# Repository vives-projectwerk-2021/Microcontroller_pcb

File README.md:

# Microcontroller_pcb

Kicad files for our microcontroller pcb

## Schematic

You can see the updated schematic of our main board in the picture below

## Pictures

| Front | Back |
|---|---|
|In this picture you can see the front of the pcb|In this picture you can see the back of the pcb
| |  |

## Components

- STM32L476RGT

- 32768 Crystal

- ESD Protection(USBLC6-2SC6)

- L432KC pin layout

- Cryptochip (ATTEC508A)

- Batteryholder(1013)

- LoraModule (RFM95W)

- Lichtsensor (LTR-329ALS)

- 2x Button switch SMD

- 18x 100nF (0603) condensatoren

- 2x 4pf (0603) Condensator bij crystal

- LED SMD (0805)

- 2x Fuse (0603)

- Temperaturesensor TCN75AVUA713-VAO

- EEPROM geheugen 24AA64T

- Connector Antenne SMA_Amphenol

- Connector voor moisture 2x03 2.54mm

- USB-C Connector 2.0 Type-c-31-m-12

- Connector voor batterij 1x03 2.54mm

- 2x Connector Molex 1x08 2.00mm

- SWD Programming port (20021521-00010T1LF)

- 2x LDO (PS1 S-1318B33-M5T1U4)

- 1x 4.7kΩ

- 2x 5.1kΩ

- 3x 360Ω

- 2x 100kΩ

- 1x 220kΩ

- 1x 330kΩ

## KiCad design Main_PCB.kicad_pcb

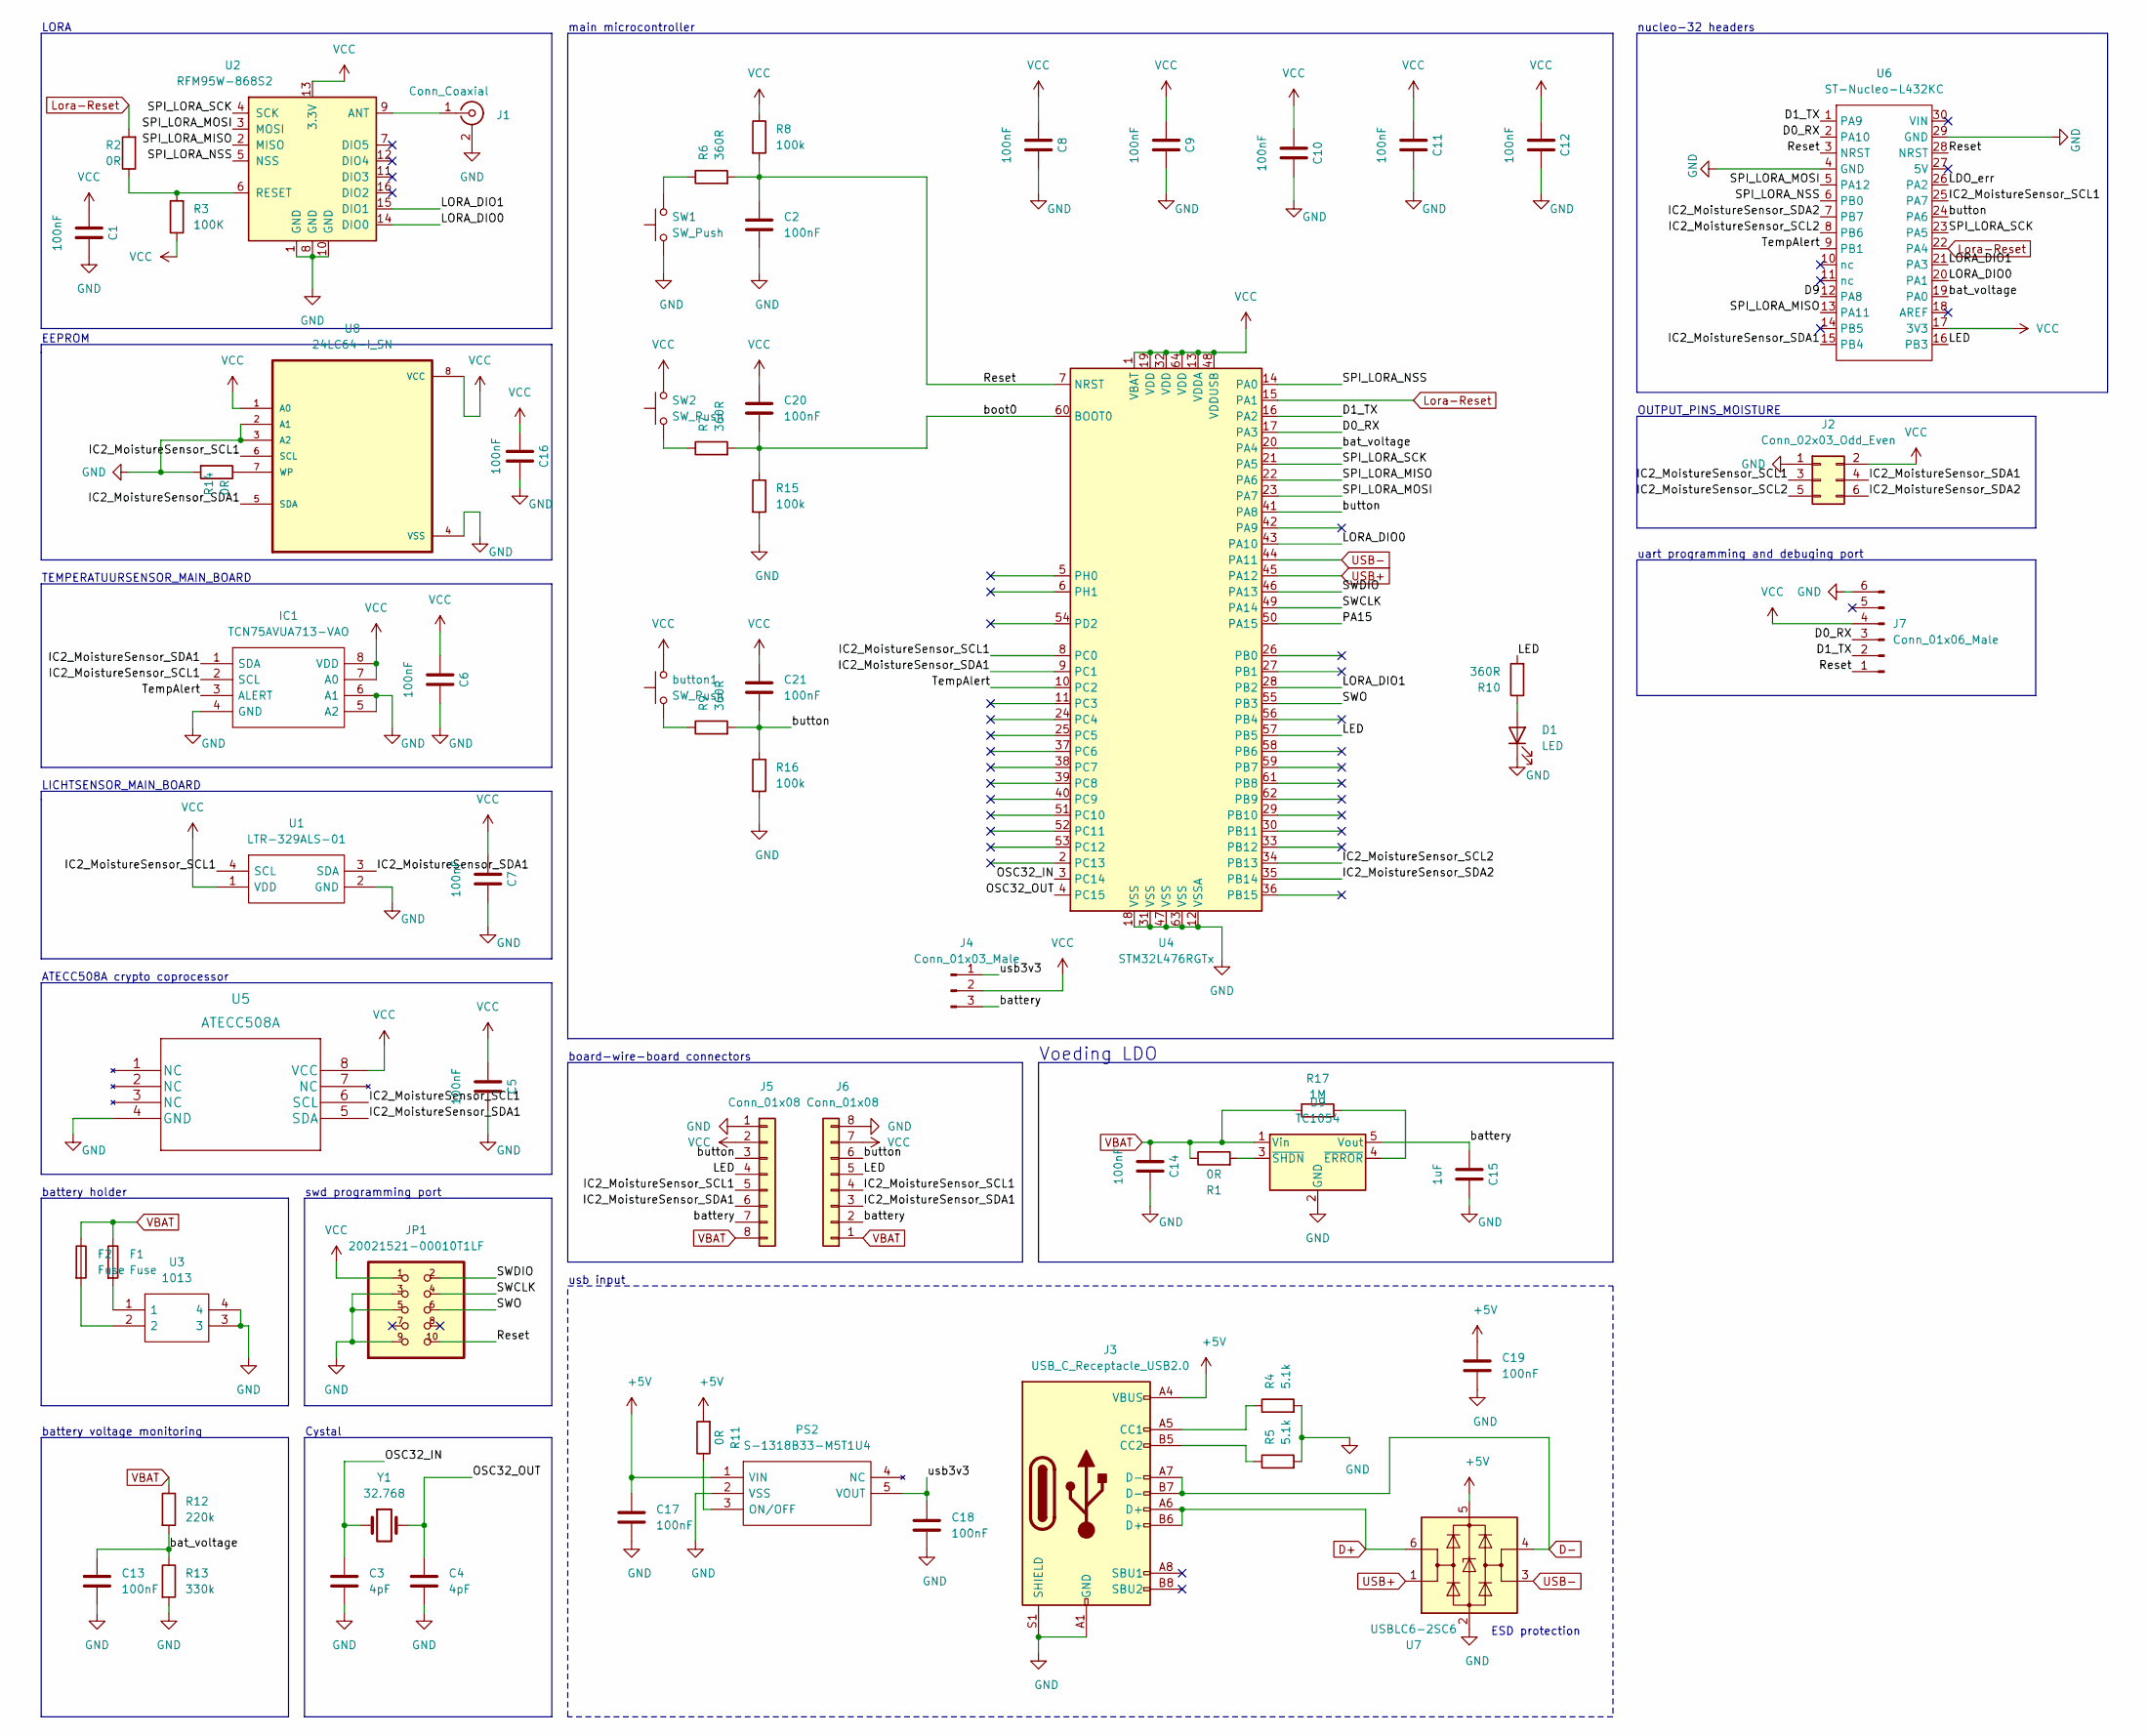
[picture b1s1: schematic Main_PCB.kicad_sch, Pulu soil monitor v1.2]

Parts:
C1, C2, C5, C6, C7, C8, C9, C10, C11, C12, C13, C14, C16, C17, C18, C19, C20, C21: 100nF; C_0603_1608Metric_Pad1.08x0.95mm_HandSolder
C3, C4: 4pF; C_0603_1608Metric_Pad1.08x0.95mm_HandSolder
C15: 1uF; C_0805_2012Metric_Pad1.18x1.45mm_HandSolder
D1: LED; LED_0805_2012Metric_Pad1.15x1.40mm_HandSolder
F1, F2: Fuse; Fuse_0603_1608Metric_Pad1.05x0.95mm_HandSolder
IC1: TCN75AVUA713-VAO; SOP65P490X110-8N; Manufacturer_Part_Number TCN75AVUA713-VAO; Mouser Part Number 579-TCN75AVUA713-VAO
J1: Conn_Coaxial; SMA_Amphenol_901-144_Vertical
J2: Conn_02x03_Odd_Even; IDC-Header_2x03_P2.54mm_Vertical
J3: USB_C_Receptacle_USB2.0; USB_C_Receptacle_HRO_TYPE-C-31-M-12
J4: Conn_01x03_Male; PinHeader_1x03_P2.54mm_Vertical
J5, J6: Conn_01x08; Molex_Micro-Latch_53253-0870_1x08_P2.00mm_Vertical
J7: Conn_01x06_Male; PinHeader_1x06_P2.54mm_Vertical
JP1: 20021521-00010T1LF
PS2: S-1318B33-M5T1U4; SOT95P275X130-5N; Manufacturer_Part_Number S-1318B33-M5T1U4; Mouser Part Number 628-S-1318B33-M5T1U4
R1, R2, R11, R14: 0R; R_0603_1608Metric_Pad0.98x0.95mm_HandSolder
R3: 100K; R_0603_1608Metric_Pad0.98x0.95mm_HandSolder
R4, R5: 5.1k; R_0603_1608Metric_Pad0.98x0.95mm_HandSolder
R6, R7, R9, R10: 360R; R_0603_1608Metric_Pad0.98x0.95mm_HandSolder
R8, R15, R16: 100k; R_0603_1608Metric_Pad0.98x0.95mm_HandSolder
R12: 220k; R_0603_1608Metric_Pad0.98x0.95mm_HandSolder
R13: 330k; R_0603_1608Metric_Pad0.98x0.95mm_HandSolder
R17: 1M; R_0612_1632Metric_Pad1.18x3.40mm_HandSolder
SW1, SW2: SW_Push; SW_SPST_TL3342
U1: LTR-329ALS-01; LTR329ALS01; Manufacturer_Part_Number LTR-329ALS-01; Mouser Part Number 859-LTR-329ALS-01
U2: RFM95W-868S2; XCVR_RFM95W-868S2
U3: 1013; Manufacturer_Part_Number 1013; Mouser Part Number 534-1013
U4: STM32L476RGTx; LQFP-64_10x10mm_P0.5mm
U5: ATECC508A; ATECC508A-SSHDA-T
U6: ST-Nucleo-L432KC
U7: USBLC6-2SC6; SOT-23-6
U8: 24LC64-I_SN; SOP-8_3.9x4.9mm_P1.27mm
U9: TC1054; SOT-23-5
Y1: 32.768; Crystal_SMD_3215-2Pin_3.2x1.5mm
button1: SW_Push; SW_SPST_TL3342

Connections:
+5V: C17.1, C19.1, J3.A4 (VBUS), J3.A9 (VBUS), J3.B4 (VBUS), J3.B9 (VBUS), PS2.1 (VIN), R11.2, U7.5 (VBUS)
/D0_RX: J7.3, U4.17 (PA3), U6.2 (PA10)
/D1_TX: J7.2, U4.16 (PA2), U6.1 (PA9)
/D9: U6.12 (PA8)
/IC2_MoistureSensor_SCL1: IC1.2 (SCL), J2.3, J5.5, J6.4, U1.4 (SCL), U4.8 (PC0), U5.6 (SCL), U6.25 (PA7), U8.6 (SCL)
/IC2_MoistureSensor_SCL2: J2.5, U4.34 (PB13), U6.8 (PB6)
/IC2_MoistureSensor_SDA1: IC1.1 (SDA), J2.4, J5.6, J6.3, U1.3 (SDA), U4.9 (PC1), U5.5 (SDA), U6.15 (PB4), U8.5 (SDA)
/IC2_MoistureSensor_SDA2: J2.6, U4.35 (PB14), U6.7 (PB7)
/LDO_err: U6.26 (PA2)
/LED: J5.4, J6.5, R10.2, U4.57 (PB5), U6.16 (PB3)
/LORA_DIO0: U2.14 (DIO0), U4.43 (PA10), U6.20 (PA1)
/LORA_DIO1: U2.15 (DIO1), U4.28 (PB2), U6.21 (PA3)
/OSC32_IN: C3.1, U4.3 (PC14), Y1.1
/OSC32_OUT: C4.1, U4.4 (PC15), Y1.2
/PA15: U4.50 (PA15)
/Reset: C2.1, J7.1, JP1.10, R6.2, R8.2, U4.7 (NRST), U6.3 (NRST), U6.28 (NRST)
/SPI_LORA_MISO: U2.2 (MISO), U4.22 (PA6), U6.13 (PA11)
/SPI_LORA_MOSI: U2.3 (MOSI), U4.23 (PA7), U6.5 (PA12)
/SPI_LORA_NSS: U2.5 (NSS), U4.14 (PA0), U6.6 (PB0)
/SPI_LORA_SCK: U2.4 (SCK), U4.21 (PA5), U6.23 (PA5)
/SWCLK: JP1.4, U4.49 (PA14)
/SWDIO: JP1.2, U4.46 (PA13)
/SWO: JP1.6, U4.55 (PB3)
/TempAlert: IC1.3 (ALERT), U4.10 (PC2), U6.9 (PB1)
/bat_voltage: C13.1, R12.2, R13.1, U4.20 (PA4), U6.19 (PA0)
/battery: C15.2, J4.3, J5.7, J6.2, U9.5 (Vout)
/boot0: C20.2, R7.2, R15.1, U4.60 (BOOT0)
/button: C21.2, J5.3, J6.6, R9.2, R16.1, U4.41 (PA8), U6.24 (PA6)
/usb3v3: C18.1, J4.1, PS2.5 (VOUT)
D+: J3.A6 (D+), J3.B6 (D+), U7.6 (I/O1)
D-: J3.A7 (D-), J3.B7 (D-), U7.4 (I/O2)
GND: C1.1, C2.2, C3.2, C4.2, C5.1, C6.1, C7.1, C8.1, C9.1, C10.1, C11.1, C12.1, C13.2, C14.1, C15.1, C16.1, C17.2, C18.2, C19.2, D1.1 (K), IC1.4 (GND), IC1.5 (A2), IC1.6 (A1), J1.2 (Ext), J2.1, J3.A1 (GND), J3.A12 (GND), J3.B1 (GND), J3.B12 (GND), J3.S1 (SHIELD), J5.1, J6.8, J7.6, JP1.3, JP1.5, JP1.9, PS2.2 (VSS), R4.2, R5.2, R13.2, R14.2, R15.2, R16.2, SW1.1, U1.2 (GND), U2.1 (GND), U2.8 (GND), U2.10 (GND), U3.3, U3.4, U4.12 (VSSA), U4.18 (VSS), U4.31 (VSS), U4.47 (VSS), U4.63 (VSS), U5.4 (GND), U6.4 (GND), U6.29 (GND), U7.2 (GND), U8.2 (A1), U8.3 (A2), U8.4 (VSS), U9.2 (GND)
Lora-Reset: R2.2, U4.15 (PA1), U6.22 (PA4)
unnamed: D1.2 (A), R10.1
unnamed: F1.2, U3.1
unnamed: F2.2, U3.2
unnamed: J1.1 (In), U2.9 (ANT)
unnamed: J3.A5 (CC1), R4.1
unnamed: J3.B5 (CC2), R5.1
unnamed: PS2.3 (ON/OFF), R11.1
unnamed: R1.2, U9.3 (~SHDN)
unnamed: R2.1, R3.2, U2.6 (RESET)
unnamed: R6.1, SW1.2
unnamed: R7.1, SW2.1
unnamed: R9.1, button1.1
unnamed: R14.1, U8.7 (WP)
unnamed: R17.1, U9.4 (~ERROR)
USB+: U4.45 (PA12), U7.1 (I/O1)
USB-: U4.44 (PA11), U7.3 (I/O2)
VBAT: C14.2, F1.1, F2.1, J5.8, J6.1, R1.1, R12.1, R17.2, U9.1 (Vin)
VCC: C1.2, C5.2, C6.2, C7.2, C8.2, C9.2, C10.2, C11.2, C12.2, C16.2, C20.1, C21.1, IC1.7 (A0), IC1.8 (VDD), J2.2, J4.2, J5.2, J6.7, J7.4, JP1.1, R3.1, R8.1, SW2.2, U1.1 (VDD), U2.13 (3.3V), U4.1 (VBAT), U4.13 (VDDA), U4.19 (VDD), U4.32 (VDD), U4.48 (VDDUSB), U4.64 (VDD), U5.8 (VCC), U6.17 (3V3), U8.1 (A0), U8.8 (VCC), button1.2

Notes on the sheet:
nucleo-32 headers
swd programming port
Voeding LDO
uart programming and debuging port
OUTPUT_PINS_MOISTURE
EEPROM
battery voltage monitoring
board-wire-board connectors
ESD protection
LORA
battery holder
LICHTSENSOR_MAIN_BOARD
ATECC508A crypto coprocessor
TEMPERATUURSENSOR_MAIN_BOARD
main microcontroller
Cystal
usb input

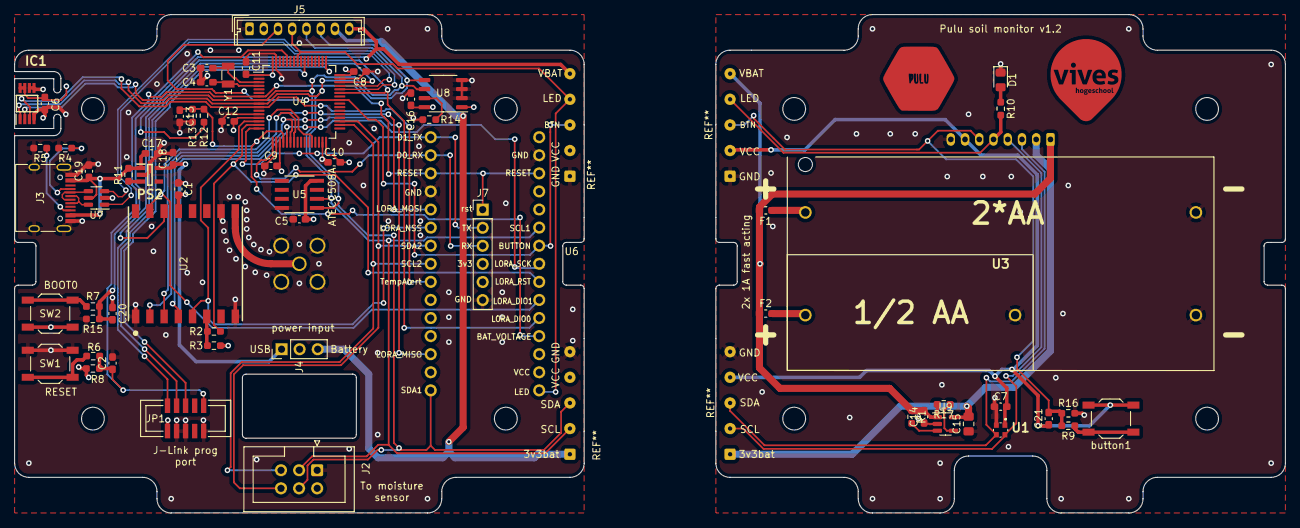
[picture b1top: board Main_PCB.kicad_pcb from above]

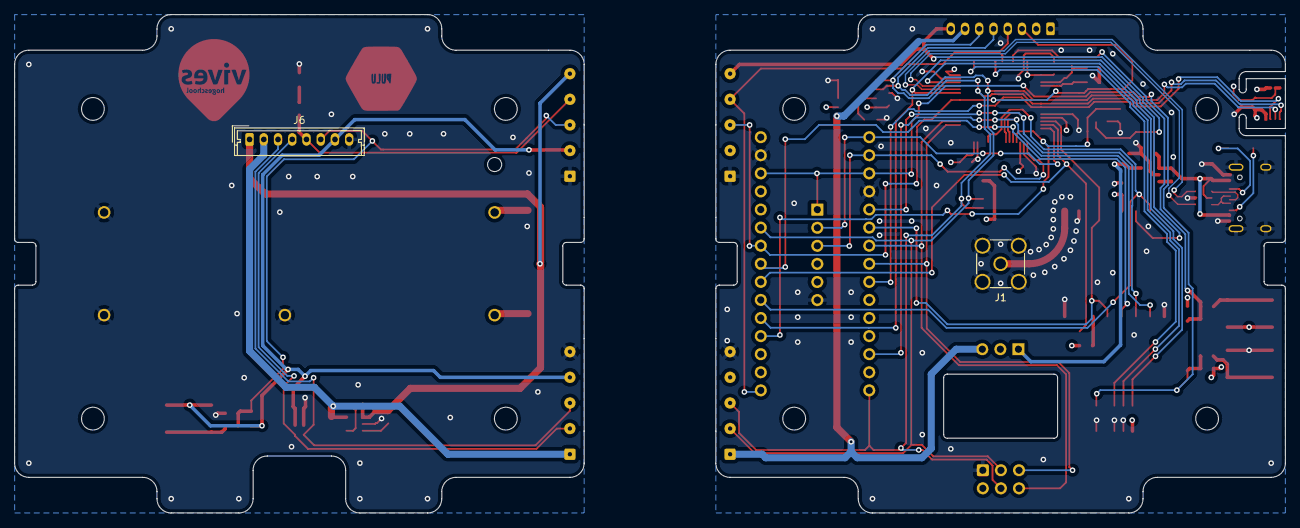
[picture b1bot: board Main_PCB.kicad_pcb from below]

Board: 4 copper layers, 178.5 x 70.0 mm, 72 parts (2 on the bottom side), 48 nets.

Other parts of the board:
REF1, REF2, REF3, REF4, REF5, REF6, REF7, REF8: MountingHole_3.2mm_M3

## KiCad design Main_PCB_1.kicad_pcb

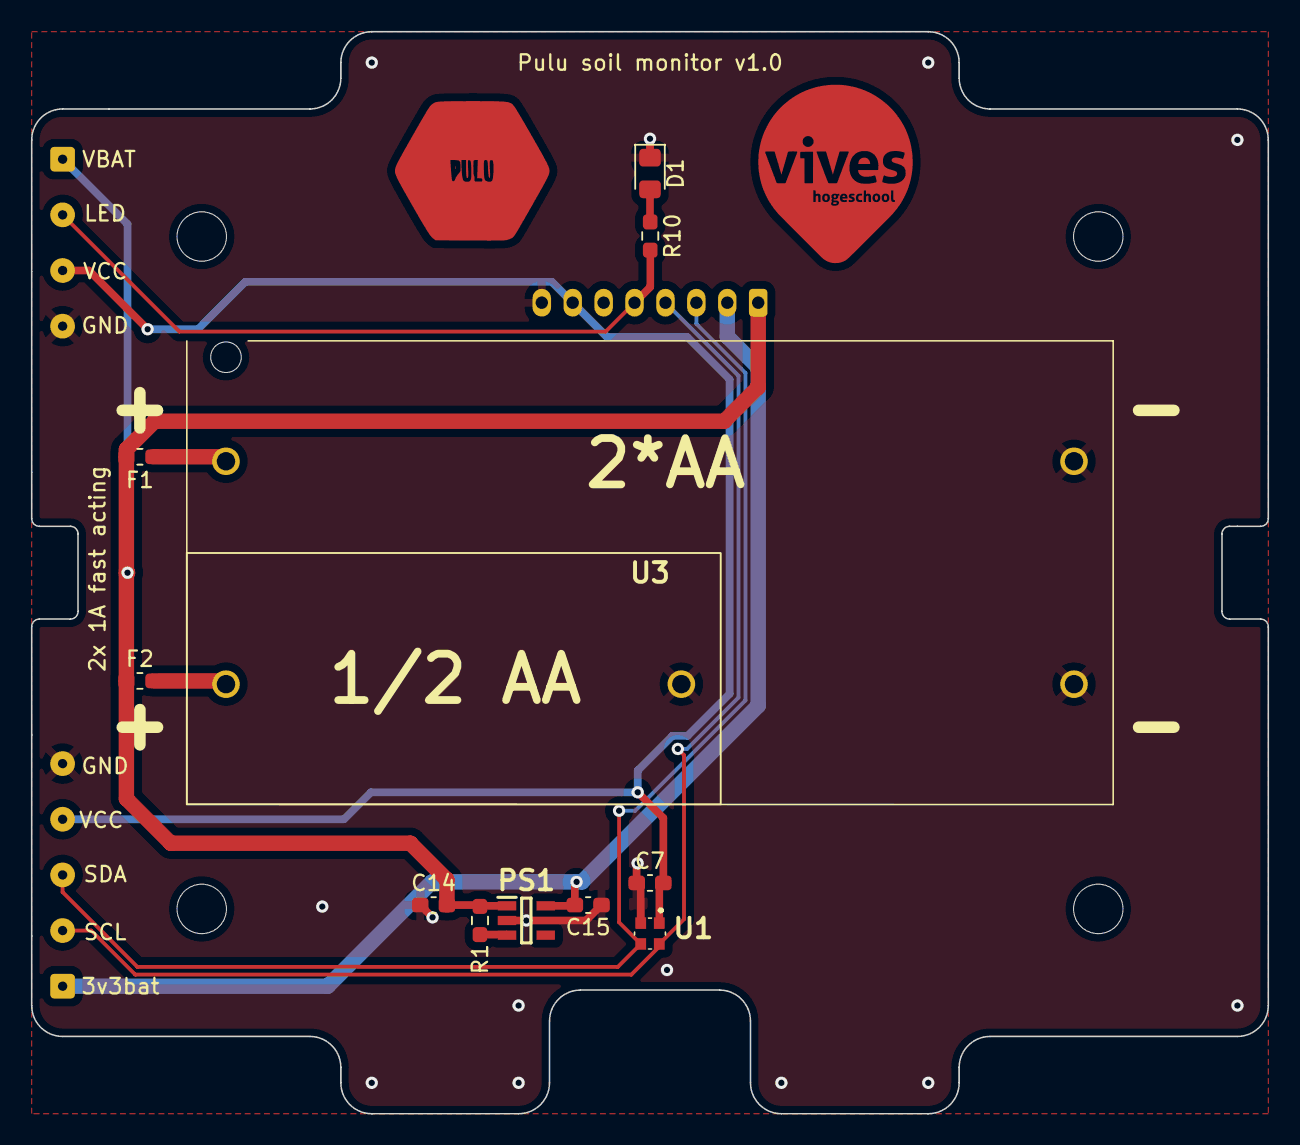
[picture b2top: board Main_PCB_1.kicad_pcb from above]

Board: 2 copper layers, 80.0 x 70.0 mm, 16 parts (1 on the bottom side), 11 nets.

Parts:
C7, C14, C15: 100nF; C_0603_1608Metric_Pad1.08x0.95mm_HandSolder
D1: LED; LED_0805_2012Metric_Pad1.15x1.40mm_HandSolder
F1, F2: Fuse; Fuse_0603_1608Metric_Pad1.05x0.95mm_HandSolder
J6: Conn_01x08; Molex_Micro-Latch_53253-0870_1x08_P2.00mm_Vertical
PS1: S-1318B33-M5T1U4; SOT95P275X130-5N
R1: 0R; R_0603_1608Metric_Pad0.98x0.95mm_HandSolder
R10: 360R; R_0603_1608Metric_Pad0.98x0.95mm_HandSolder
REF5, REF6, REF7, REF8: MountingHole_3.2mm_M3
U1: LTR-329ALS-01; LTR329ALS01
U3: 1013

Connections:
/IC2_MoistureSensor_SCL1: J6.4, U1.4 (SCL)
/IC2_MoistureSensor_SDA1: J6.3, U1.3 (SDA)
/LED: J6.5, R10.2
/battery: C15.2, J6.2, PS1.5 (VOUT)
GND: C7.1, C14.1, C15.1, D1.1 (K), J6.8, PS1.2 (VSS), U1.2 (GND), U3.3, U3.4
unnamed: D1.2 (A), R10.1
unnamed: F1.2, U3.1
unnamed: F2.2, U3.2
unnamed: PS1.3 (ON/OFF), R1.2
VBAT: C14.2, F1.1, F2.1, J6.1, PS1.1 (VIN), R1.1
VCC: C7.2, J6.7, U1.1 (VDD)

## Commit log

2021-10-08 started microcontroller pcb added lora, EEPROM, ArduinoHeaders and OUTPUTPINS
2021-10-08 fixed microcontroller
2021-10-08 added connector for moisture sensor + connected arduino header 2 microcontroller
2021-10-08 added battery holder and swd programming port
2021-10-11 assigned footprints
2021-10-15 did alot of the routing and pcb layout
2021-10-15 added some 3d files and pcb updates
2021-10-16 added images to readme
2021-10-17 finished pcb
2021-10-17 updated b2b connector
2021-10-18 made drc complete
2021-10-19 updated eeprom footprint
2021-10-22 separated pcb desgin into two
2021-10-22 added battery 3d model and exported to blender for rendering
2021-10-29 made pcb order ready and ordered on jlcpcb
2021-11-15 made BOM
2021-11-20 added general purpose button and updated layout
2021-11-23 updated ldo
2021-11-23 Revert "updated ldo"
    This reverts commit d625362cbb52fab2f45e5e3217d36f091f724f2e.
2021-11-23 updated ldo and fixed git mistake
2021-11-23 updated schematic image
2021-12-19 updated version names

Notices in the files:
parts and their libraries:
Copyright 2021 Accelerated Designs. All rights reserved.
